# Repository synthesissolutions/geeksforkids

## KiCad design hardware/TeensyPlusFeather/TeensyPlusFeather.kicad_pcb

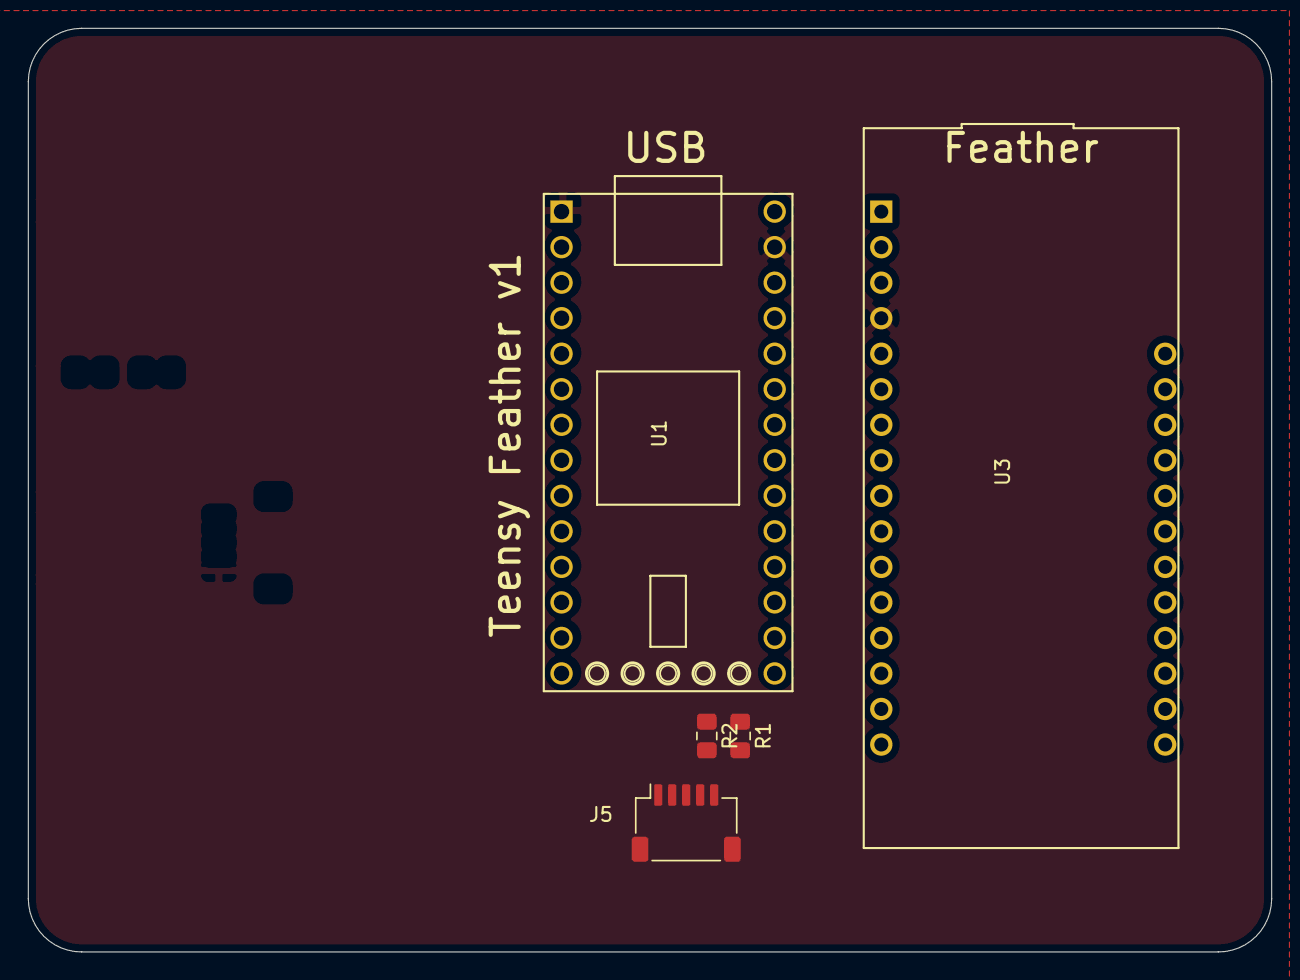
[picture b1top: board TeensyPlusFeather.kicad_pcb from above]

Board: 2 copper layers, 88.9 x 66.0 mm, 5 parts (0 on the bottom side), 21 nets, no tracks yet.

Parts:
J5: I2C; JST_SH_SM05B-SRSS-TB_1x05-1MP_P1.00mm_Horizontal
R1, R2: 10K; R_0805_2012Metric_Pad1.15x1.40mm_HandSolder
U1: Teensy4.0_NoMid; Teensy40_NoMid
U3: OLED Feather; Feather_nRF52840

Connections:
+3V3: J5.2, U1.26, U3.2
+5V: U1.28, U3.26
A0: U1.16, U3.5
A1: U1.17, U3.6
A2: U1.18, U3.7
A3: U1.19, U3.8
D2: U1.4, U3.16
D5: U1.7, U3.19
D6: U1.8, U3.20
D9: U1.11, U3.21
D10: U1.12, U3.22
D11: U1.13, U3.23
GND: J5.1, U1.1, U1.27, U3.4
I2C_SCL: R1.1, U1.21, U3.10, U3.18
I2C_SDA: R2.1, U1.20, U3.9, U3.17
MI: U1.14, U3.13, U3.24
unnamed: J5.3, R2.2
unnamed: J5.4, R1.2
RX: U1.2, U3.14
SCK: U1.15, U3.11, U3.25
TX: U1.3, U3.15

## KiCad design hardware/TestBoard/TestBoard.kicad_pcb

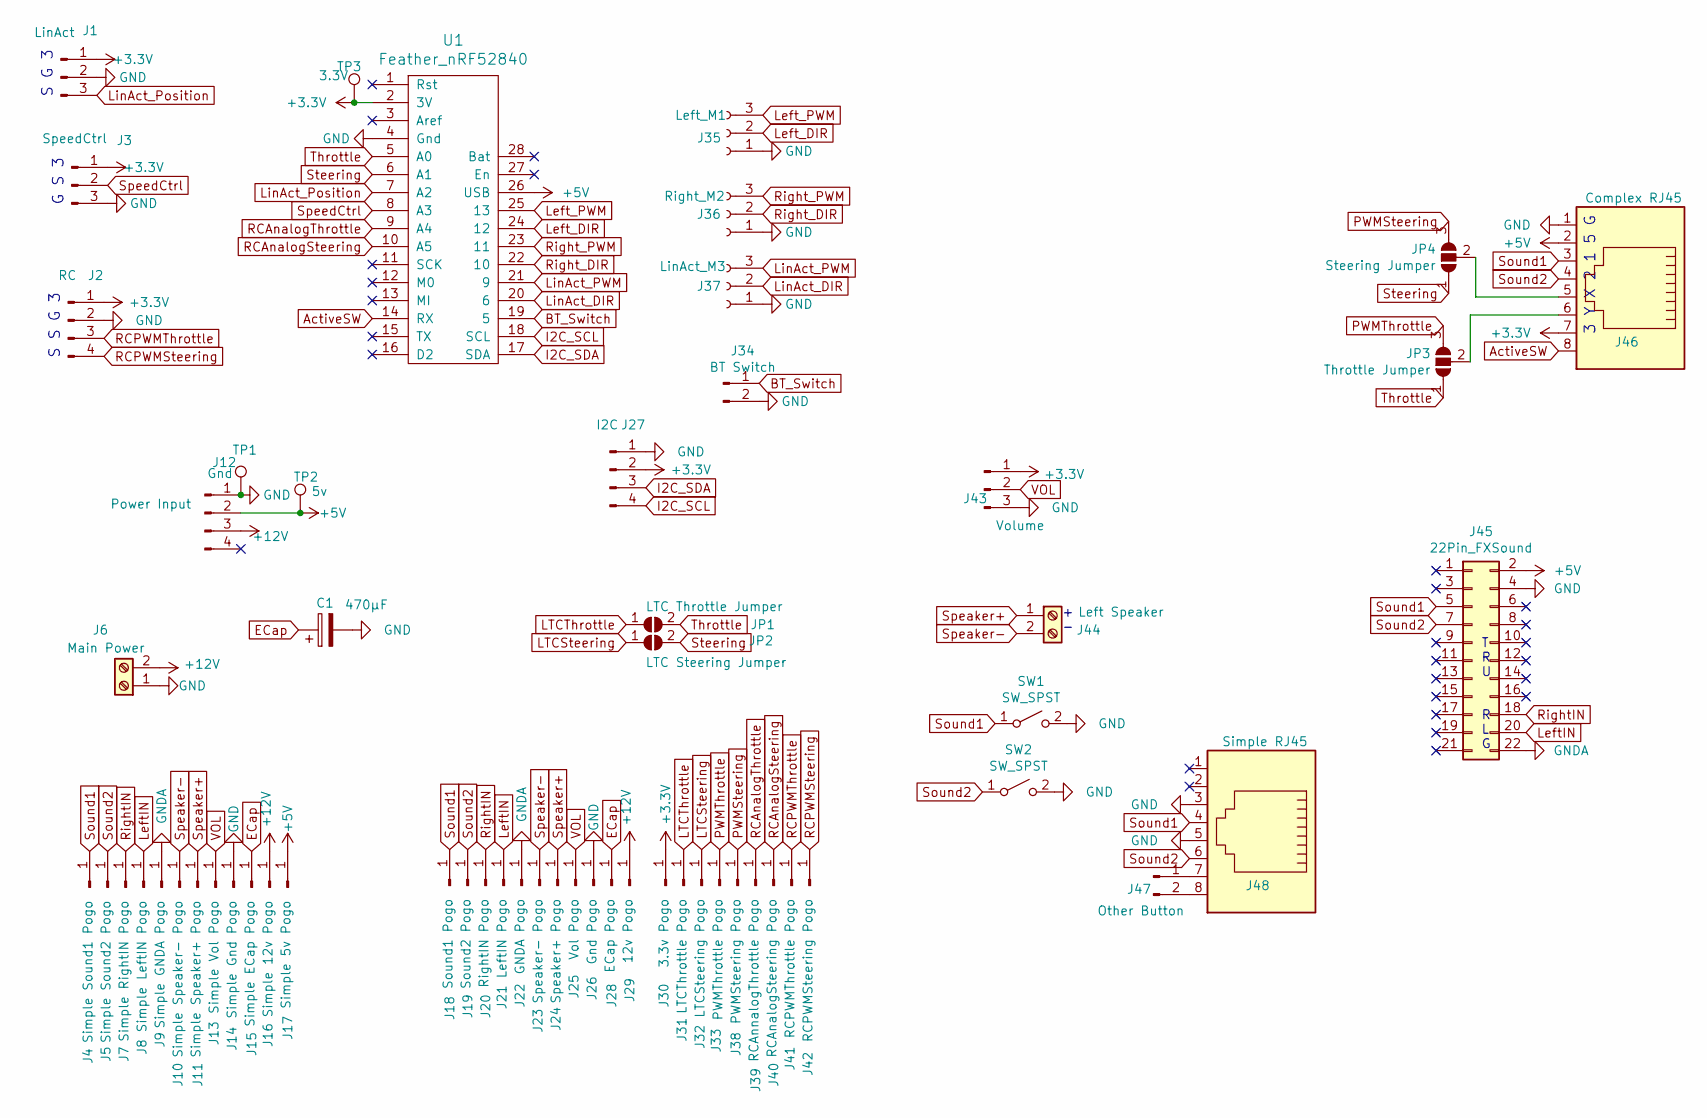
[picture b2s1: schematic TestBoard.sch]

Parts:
C1: 470µF; CP_Radial_D8.0mm_P3.50mm; DigiKey ID 1189-1859-ND
J1: LinAct; PinHeader_1x03_P2.54mm_Vertical
J2: RC; PinHeader_1x04_P2.54mm_Vertical
J3: SpeedCtrl; PinHeader_1x03_P2.54mm_Vertical
J4: Simple Sound1 Pogo; PinHeader_1x01_P2.54mm_Vertical
J5: Simple Sound2 Pogo; PinHeader_1x01_P2.54mm_Vertical
J6: Main Power; TerminalBlock_bornier-2_P5.08mm
J7: Simple RightIN Pogo; PinHeader_1x01_P2.54mm_Vertical
J8: Simple LeftIN Pogo; PinHeader_1x01_P2.54mm_Vertical
J9: Simple GNDA Pogo; PinHeader_1x01_P2.54mm_Vertical
J10: Simple Speaker- Pogo; PinHeader_1x01_P2.54mm_Vertical
J11: Simple Speaker+ Pogo; PinHeader_1x01_P2.54mm_Vertical
J12: Power Input; PinHeader_1x04_P2.54mm_Horizontal
J13: Simple Vol Pogo; PinHeader_1x01_P2.54mm_Vertical
J14: Simple Gnd Pogo; PinHeader_1x01_P2.54mm_Vertical
J15: Simple ECap Pogo; PinHeader_1x01_P2.54mm_Vertical
J16: Simple 12v Pogo; PinHeader_1x01_P2.54mm_Vertical
J17: Simple 5v Pogo; PinHeader_1x01_P2.54mm_Vertical
J18: Sound1 Pogo; PinHeader_1x01_P2.54mm_Vertical
J19: Sound2 Pogo; PinHeader_1x01_P2.54mm_Vertical
J20: RightIN Pogo; PinHeader_1x01_P2.54mm_Vertical
J21: LeftIN Pogo; PinHeader_1x01_P2.54mm_Vertical
J22: GNDA Pogo; PinHeader_1x01_P2.54mm_Vertical
J23: Speaker- Pogo; PinHeader_1x01_P2.54mm_Vertical
J24: Speaker+ Pogo; PinHeader_1x01_P2.54mm_Vertical
J25: Vol Pogo; PinHeader_1x01_P2.54mm_Vertical
J26: Gnd Pogo; PinHeader_1x01_P2.54mm_Vertical
J27: I2C; PinHeader_1x04_P2.54mm_Vertical
J28: ECap Pogo; PinHeader_1x01_P2.54mm_Vertical
J29: 12v Pogo; PinHeader_1x01_P2.54mm_Vertical
J30: 3.3v Pogo; PinHeader_1x01_P2.54mm_Vertical
J31: LTCThrottle Pogo; PinHeader_1x01_P2.54mm_Vertical
J32: LTCSteering Pogo; PinHeader_1x01_P2.54mm_Vertical
J33: PWMThrottle Pogo; PinHeader_1x01_P2.54mm_Vertical
J34: BT Switch; PinHeader_1x02_P2.54mm_Vertical
J35: Left_M1; PinHeader_1x03_P2.54mm_Vertical
J36: Right_M2; PinHeader_1x03_P2.54mm_Vertical
J37: LinAct_M3; PinHeader_1x03_P2.54mm_Vertical
J38: PWMSteering Pogo; PinHeader_1x01_P2.54mm_Vertical
J39: RCAnnalogThrottle Pogo; PinHeader_1x01_P2.54mm_Vertical
J40: RCAnalogSteering Pogo; PinHeader_1x01_P2.54mm_Vertical
J41: RCPWMThrottle Pogo; PinHeader_1x01_P2.54mm_Vertical
J42: RCPWMSteering Pogo; PinHeader_1x01_P2.54mm_Vertical
J43: Volume; PinHeader_1x03_P2.54mm_Vertical
J44: Left Speaker; TerminalBlock_bornier-2_P5.08mm
J45: 22Pin_FXSound; FXSound_2x11_P2.54mm_Short
J46: Complex RJ45; RJ45_x08_Tab_Up
J47: Other Button; PinHeader_1x02_P2.54mm_Vertical
J48: Simple RJ45; RJ45_x08_Tab_Up
JP1: LTC Throttle Jumper; PinHeader_1x02_P2.54mm_Vertical
JP2: LTC Steering Jumper; PinHeader_1x02_P2.54mm_Vertical
JP3: Throttle Jumper; PinHeader_1x03_P2.54mm_Vertical
JP4: Steering Jumper; PinHeader_1x03_P2.54mm_Vertical
SW1, SW2: SW_SPST; SW_PUSH_6mm
TP1: Gnd; TestPoint_Pad_1.5x1.5mm
TP2: 5v; TestPoint_Pad_1.5x1.5mm
TP3: 3.3V; TestPoint_Pad_1.5x1.5mm
U1: Feather_nRF52840

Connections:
+3V3: J1.1, J2.1, J3.1, J27.2, J30.1, J43.1, J46.7, TP3.1, U1.2 (3V)
+5V: J12.2, J17.1, J45.2, J46.2, TP2.1, U1.26 (USB)
+12V: J6.2, J12.3, J16.1, J29.1
ActiveSW: J46.8, U1.14 (RX)
BT_Switch: J34.1, U1.19 (5)
ECap: C1.1, J15.1, J28.1
GND: C1.2, J1.2, J2.2, J3.3, J6.1, J12.1, J14.1, J26.1, J27.1, J34.2, J35.1, J36.1, J37.1, J43.3, J45.4, J46.1, J48.3, J48.5, SW1.2 (B), SW2.2 (B), TP1.1, U1.4 (Gnd)
GNDA: J9.1, J22.1, J45.22
I2C_SCL: J27.4, U1.18 (SCL)
I2C_SDA: J27.3, U1.17 (SDA)
LTCSteering: J32.1, JP2.1 (A)
LTCThrottle: J31.1, JP1.1 (A)
LeftIN: J8.1, J21.1, J45.20
Left_DIR: J35.2, U1.24 (12)
Left_PWM: J35.3, U1.25 (13)
LinAct_DIR: J37.2, U1.20 (6)
LinAct_PWM: J37.3, U1.21 (9)
LinAct_Position: J1.3, U1.7 (A2)
unnamed: J46.5, JP4.2 (C)
unnamed: J46.6, JP3.2 (C)
unnamed: J47.1, J48.7
unnamed: J47.2, J48.8
PWMSteering: J38.1, JP4.3 (B)
PWMThrottle: J33.1, JP3.3 (B)
RCAnalogSteering: J40.1, U1.10 (A5)
RCAnalogThrottle: J39.1, U1.9 (A4)
RCPWMSteering: J2.4, J42.1
RCPWMThrottle: J2.3, J41.1
RightIN: J7.1, J20.1, J45.18
Right_DIR: J36.2, U1.22 (10)
Right_PWM: J36.3, U1.23 (11)
Sound1: J4.1, J18.1, J45.5, J46.3, J48.4, SW1.1 (A)
Sound2: J5.1, J19.1, J45.7, J46.4, J48.6, SW2.1 (A)
Speaker+: J11.1, J24.1, J44.1
Speaker-: J10.1, J23.1, J44.2
SpeedCtrl: J3.2, U1.8 (A3)
Steering: JP2.2 (B), JP4.1 (A), U1.6 (A1)
Throttle: JP1.2 (B), JP3.1 (A), U1.5 (A0)
VOL: J13.1, J25.1, J43.2

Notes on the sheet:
3 Y X 2 1 5 G
S S G 3
G S 3
S G 3
R L G
T R U
+ -

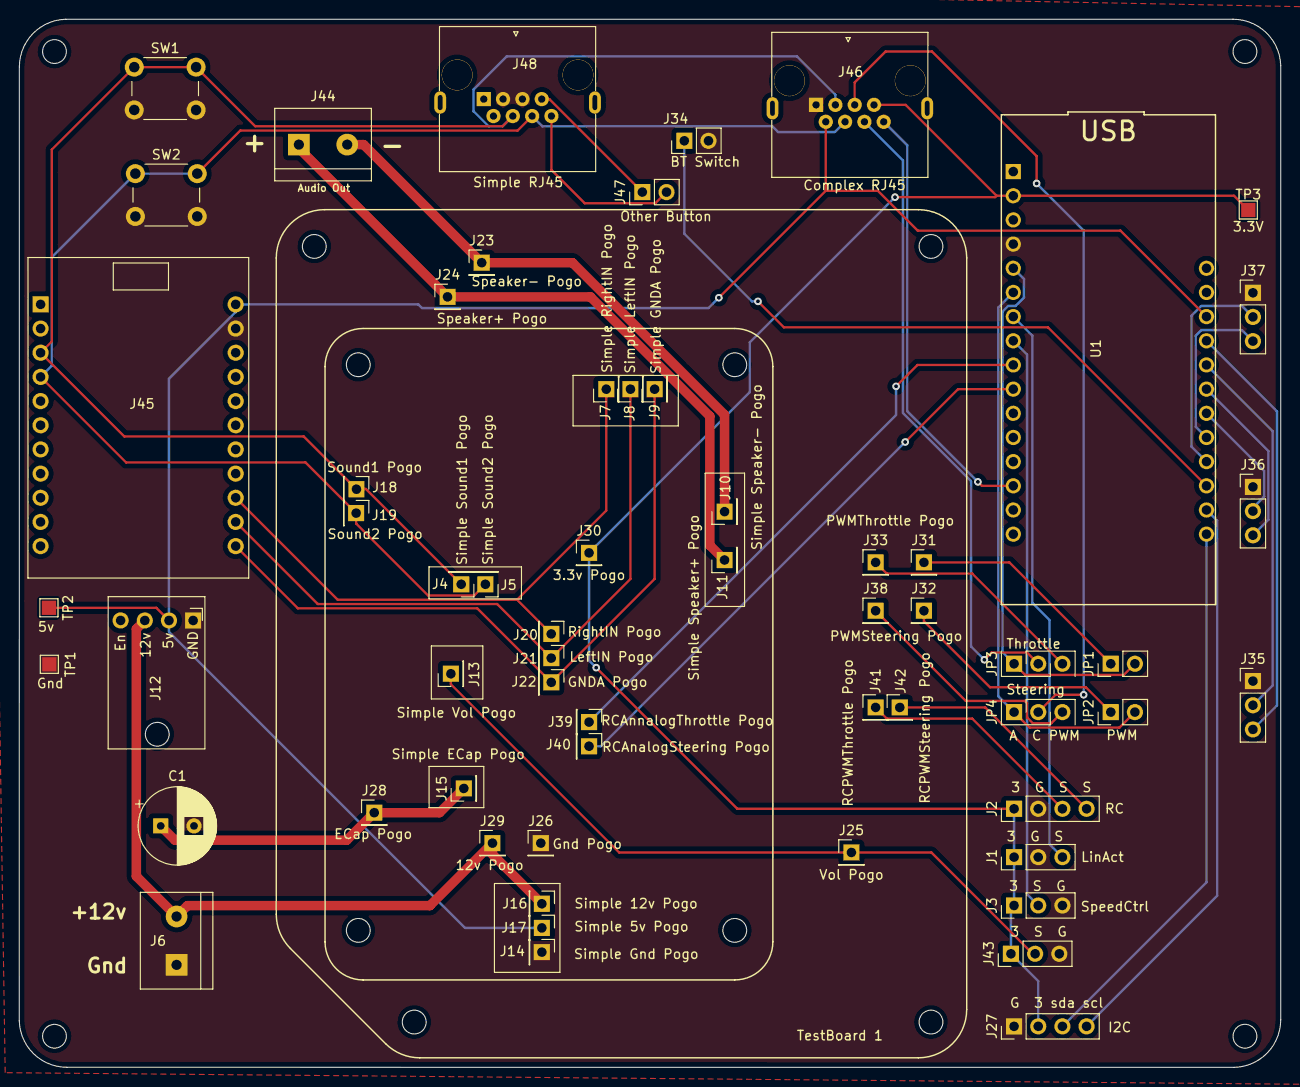
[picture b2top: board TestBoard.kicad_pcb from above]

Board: 2 copper layers, 132.6 x 110.1 mm, 63 parts (0 on the bottom side), 39 nets.

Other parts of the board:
REF: MountingHole_2.5mm
REF#2, REF#3, REF#4: MountingHole_2.5mm

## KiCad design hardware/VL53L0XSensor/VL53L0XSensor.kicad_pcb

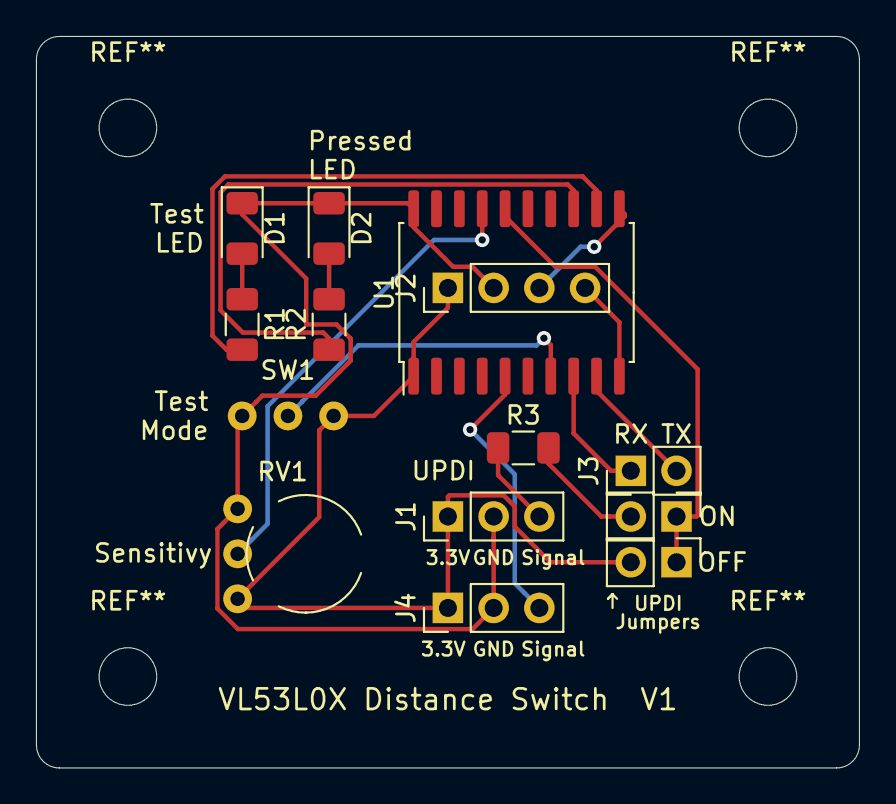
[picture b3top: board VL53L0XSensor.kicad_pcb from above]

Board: 2 copper layers, 45.7 x 40.6 mm, 14 parts (0 on the bottom side), 16 nets.

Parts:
D1: Mode LED; LED_1206_3216Metric
D2: Button LED; LED_1206_3216Metric
J1, J4: Conn_01x03_Male; PinHeader_1x03_P2.54mm_Vertical
J2: Conn_01x04_Female; PinHeader_1x04_P2.54mm_Vertical
J3: Conn_01x02_Male; PinHeader_1x02_P2.54mm_Vertical
OFF: Jumper_NO_Small; PinHeader_1x02_P2.54mm_Vertical
ON: Jumper_NO_Small; PinHeader_1x02_P2.54mm_Vertical
R1, R2: 220; R_1206_3216Metric
R3: 4.7k; R_1206_3216Metric
RV1: R_POT; Potentiometer_Small_Blue
SW1: SW_SPDT; Switch_THT_SPDT
U1: ATtiny3216-S; SOIC-20W_7.5x12.8mm_P1.27mm

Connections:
+3V3: J1.1, J2.1, J4.1, OFF.2, RV1.1, SW1.3, U1.1
GND: D1.1, D2.1, J1.2, J2.2, J4.2, RV1.3, SW1.1, U1.20
unnamed: D1.2, R1.1
unnamed: D2.2, R2.2
unnamed: J1.3, R3.1
unnamed: J2.3, U1.11
unnamed: J2.4, U1.10
unnamed: J3.1, U1.8
unnamed: J3.2, U1.9
unnamed: J4.3, U1.5
unnamed: OFF.1, ON.1, U1.16
unnamed: ON.2, R3.2
unnamed: R1.2, U1.12
unnamed: R2.1, U1.13
unnamed: RV1.2, U1.17
unnamed: SW1.2, U1.7

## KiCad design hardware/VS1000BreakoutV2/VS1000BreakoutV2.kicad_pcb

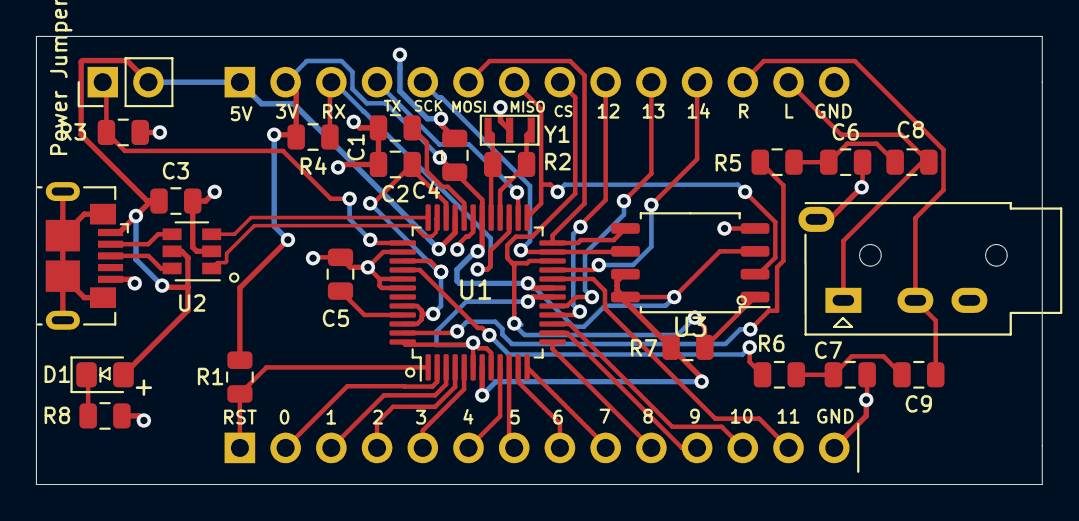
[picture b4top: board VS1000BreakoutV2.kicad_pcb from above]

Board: 2 copper layers, 55.9 x 24.9 mm, 27 parts (0 on the bottom side), 42 nets.

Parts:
C1, C2, C3, C4, C8, C9: 10uF; C_0805_2012Metric
C5: 1uF; C_0805_2012Metric
C6, C7: 4.7nF; C_0805_2012Metric
D1: Power; LED_0805_2012Metric_Pad1.15x1.40mm_HandSolder
J1: Power Jumper; PinHeader_1x02_P2.54mm_Vertical
J2, J4: Conn_01x14_Male; PinHeader_1x14_P2.54mm_Vertical
J3: USB_B_Micro; USB_Micro-B_GCT_USB3076-30-A
J5: AudioJack4; Jack_3.5mm_PJ320A_Horizontal
R1, R4, R7: 100K; R_0805_2012Metric
R2, R3: 1M; R_0805_2012Metric
R5, R6, R8: 470; R_0805_2012Metric
U1: VS1000; LQFP-48_7x7mm_P0.5mm
U2: USBLC6-2SC6; SOT-23-6
U3: MX25L6473FM2I-08G; SOIC-8_5.275x5.275mm_P1.27mm
Y1: 12MHz; Resonator

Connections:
+5V: C3.1, D1.2, J1.2, J3.1, J4.1, U1.33, U2.5
CS: J4.8, R7.2, U1.22, U3.1
GND: C1.2, C2.2, C3.2, C4.1, C5.1, C6.2, C7.2, J2.14, J3.5, J4.14, J5.S, R3.2, R8.2, U1.6, U1.8, U1.18, U1.31, U1.38, U1.41, U1.42, U1.48, U2.2, U3.4, Y1.2
GPIO_0: J2.2, U1.2
GPIO_1: J2.3, U1.3
GPIO_2: J2.4, U1.4
GPIO_3: J2.5, U1.5
GPIO_4: J2.6, U1.9
GPIO_5: J2.7, U1.10
GPIO_6: J2.8, U1.11
GPIO_7: J2.9, U1.12
GPIO_8: J2.10, U1.13
GPIO_9: J2.11, U1.14
GPIO_10: J2.12, U1.15
GPIO_11: J2.13, U1.20
GPIO_12: J4.9, U1.16
GPIO_13: J4.10, U1.17
GPIO_14: J4.11, U1.21
LEFT: R5.2, U1.47
L_AC: C8.1, J4.13, J5.T
MISO: J4.7, U1.25, U3.2
MOSI: J4.6, U1.24, U3.5
unnamed: C4.2, U1.32
unnamed: C5.2, U1.45
unnamed: C6.1, C8.2, R5.1
unnamed: C7.1, C9.2, R6.1
unnamed: D1.1, R8.1
unnamed: J1.1, R3.1, U1.37
unnamed: R2.1, U1.29, Y1.3
unnamed: R2.2, U1.28, Y1.1
RESET: J2.1, R1.1, U1.1
RIGHT: R6.2, U1.40
RX: J4.3, R4.1, U1.27
R_AC: C9.1, J4.12, J5.R1
SCK: J4.5, U1.23, U3.6
TX: J4.4, U1.26
USB_CONN_D+: J3.3, U2.6
USB_CONN_D-: J3.2, U2.4
USB_D+: U1.35, U2.1
USB_D-: U1.36, U2.3
VDD: C1.1, J4.2, R1.2, R4.2, R7.1, U1.7, U1.19, U1.30, U3.3, U3.7, U3.8
VDDA: C2.1, U1.34, U1.39, U1.44, U1.46

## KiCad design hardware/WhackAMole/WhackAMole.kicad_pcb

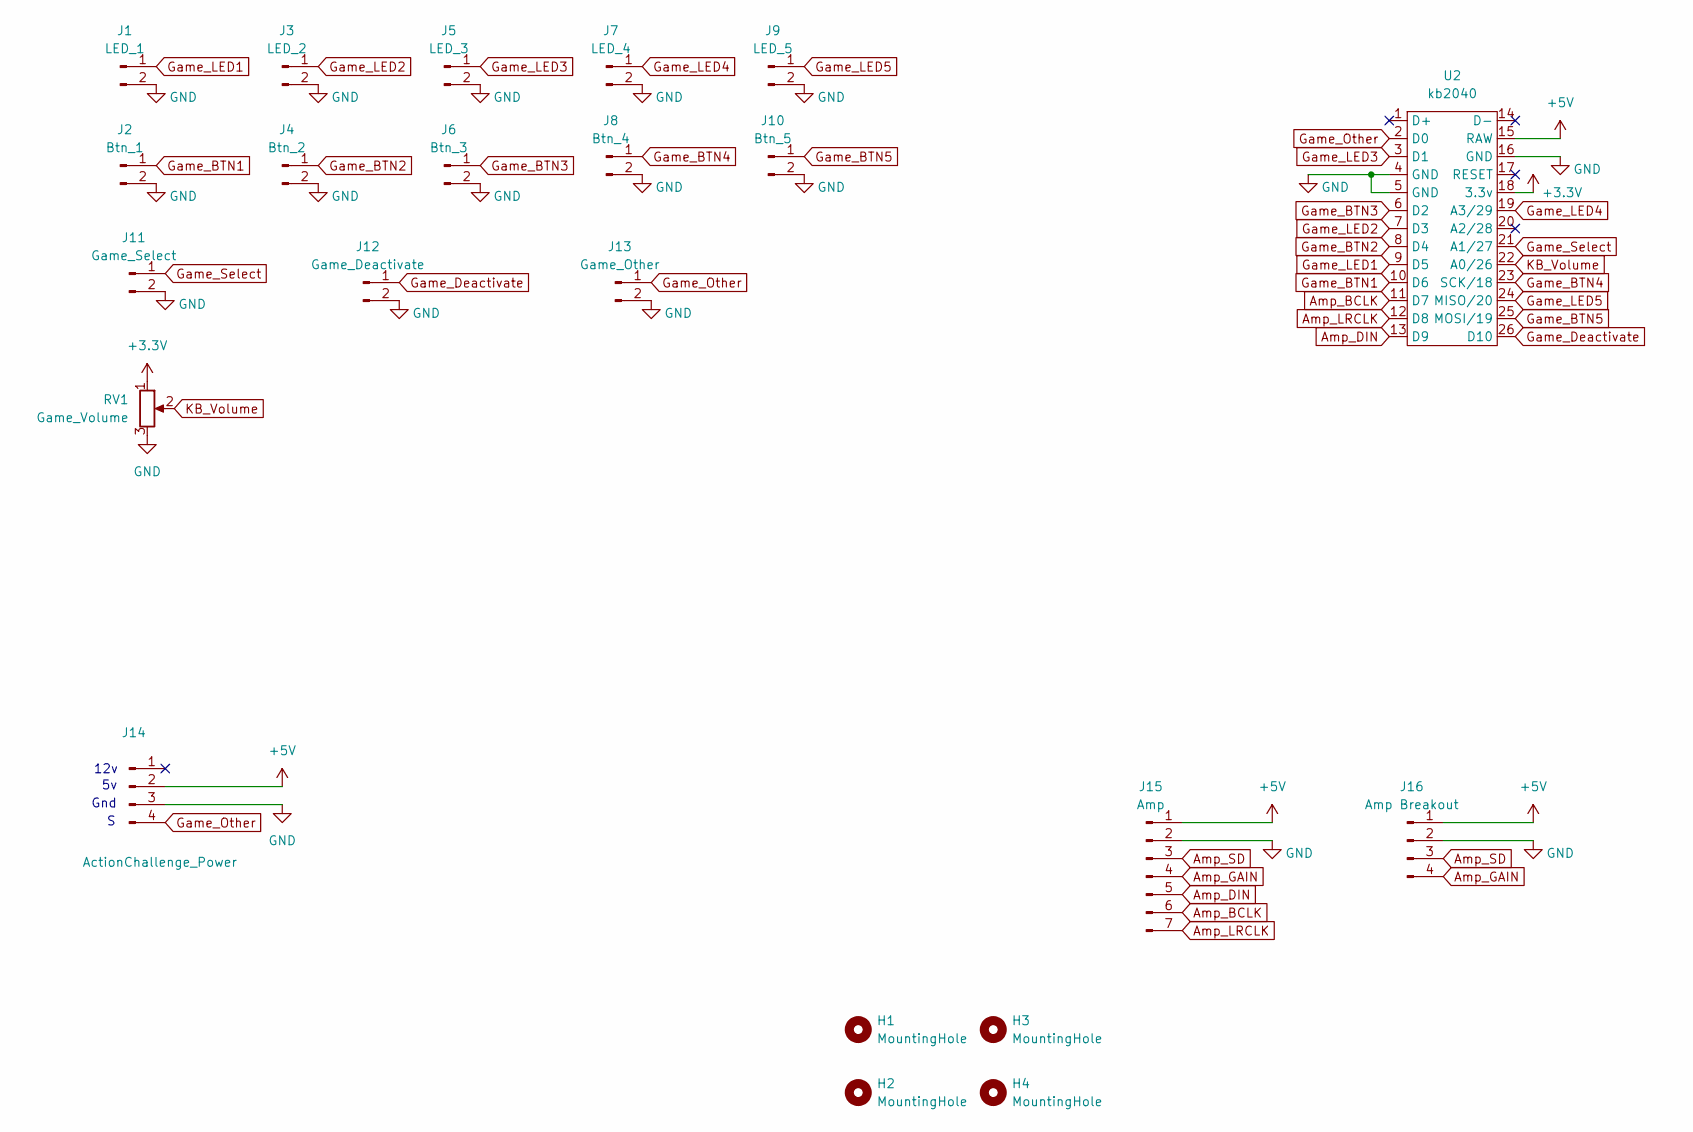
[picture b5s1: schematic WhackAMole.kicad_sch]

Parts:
H1, H2, H3, H4: MountingHole; MountingHole_2.7mm_M2.5
J1: LED_1; JST_XH_B2B-XH-A_1x02_P2.50mm_Vertical
J2: Btn_1; JST_XH_B2B-XH-A_1x02_P2.50mm_Vertical
J3: LED_2; JST_XH_B2B-XH-A_1x02_P2.50mm_Vertical
J4: Btn_2; JST_XH_B2B-XH-A_1x02_P2.50mm_Vertical
J5: LED_3; JST_XH_B2B-XH-A_1x02_P2.50mm_Vertical
J6: Btn_3; JST_XH_B2B-XH-A_1x02_P2.50mm_Vertical
J7: LED_4; JST_XH_B2B-XH-A_1x02_P2.50mm_Vertical
J8: Btn_4; JST_XH_B2B-XH-A_1x02_P2.50mm_Vertical
J9: LED_5; JST_XH_B2B-XH-A_1x02_P2.50mm_Vertical
J10: Btn_5; JST_XH_B2B-XH-A_1x02_P2.50mm_Vertical
J11: Game_Select; JST_XH_B2B-XH-A_1x02_P2.50mm_Vertical
J12: Game_Deactivate; JST_XH_B2B-XH-A_1x02_P2.50mm_Vertical
J13: Game_Other; PinSocket_1x02_P2.54mm_Vertical
J14: ActionChallenge_Power; JST_XH_B4B-XH-A_1x04_P2.50mm_Vertical
J15: Amp; Adafruit_Max98357A_Breakout
J16: Amp Breakout; PinHeader_1x04_P2.54mm_Vertical
RV1: Game_Volume; JST_XH_B3B-XH-A_1x03_P2.50mm_Vertical
U2: kb2040

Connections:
+3.3V: RV1.1, U2.18 (3.3v)
+5V: J14.2, J15.1, J16.1, U2.15 (RAW)
Amp_BCLK: J15.6, U2.11 (D7)
Amp_DIN: J15.5, U2.13 (D9)
Amp_GAIN: J15.4, J16.4
Amp_LRCLK: J15.7, U2.12 (D8)
Amp_SD: J15.3, J16.3
GND: J1.2, J2.2, J3.2, J4.2, J5.2, J6.2, J7.2, J8.2, J9.2, J10.2, J11.2, J12.2, J13.2, J14.3, J15.2, J16.2, RV1.3, U2.4 (GND), U2.5 (GND), U2.16 (GND)
Game_BTN1: J2.1, U2.10 (D6)
Game_BTN2: J4.1, U2.8 (D4)
Game_BTN3: J6.1, U2.6 (D2)
Game_BTN4: J8.1, U2.23 (SCK/18)
Game_BTN5: J10.1, U2.25 (MOSI/19)
Game_Deactivate: J12.1, U2.26 (D10)
Game_LED1: J1.1, U2.9 (D5)
Game_LED2: J3.1, U2.7 (D3)
Game_LED3: J5.1, U2.3 (D1)
Game_LED4: J7.1, U2.19 (A3/29)
Game_LED5: J9.1, U2.24 (MISO/20)
Game_Other: J13.1, J14.4, U2.2 (D0)
Game_Select: J11.1, U2.21 (A1/27)
KB_Volume: RV1.2, U2.22 (A0/26)

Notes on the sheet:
Gnd
12v

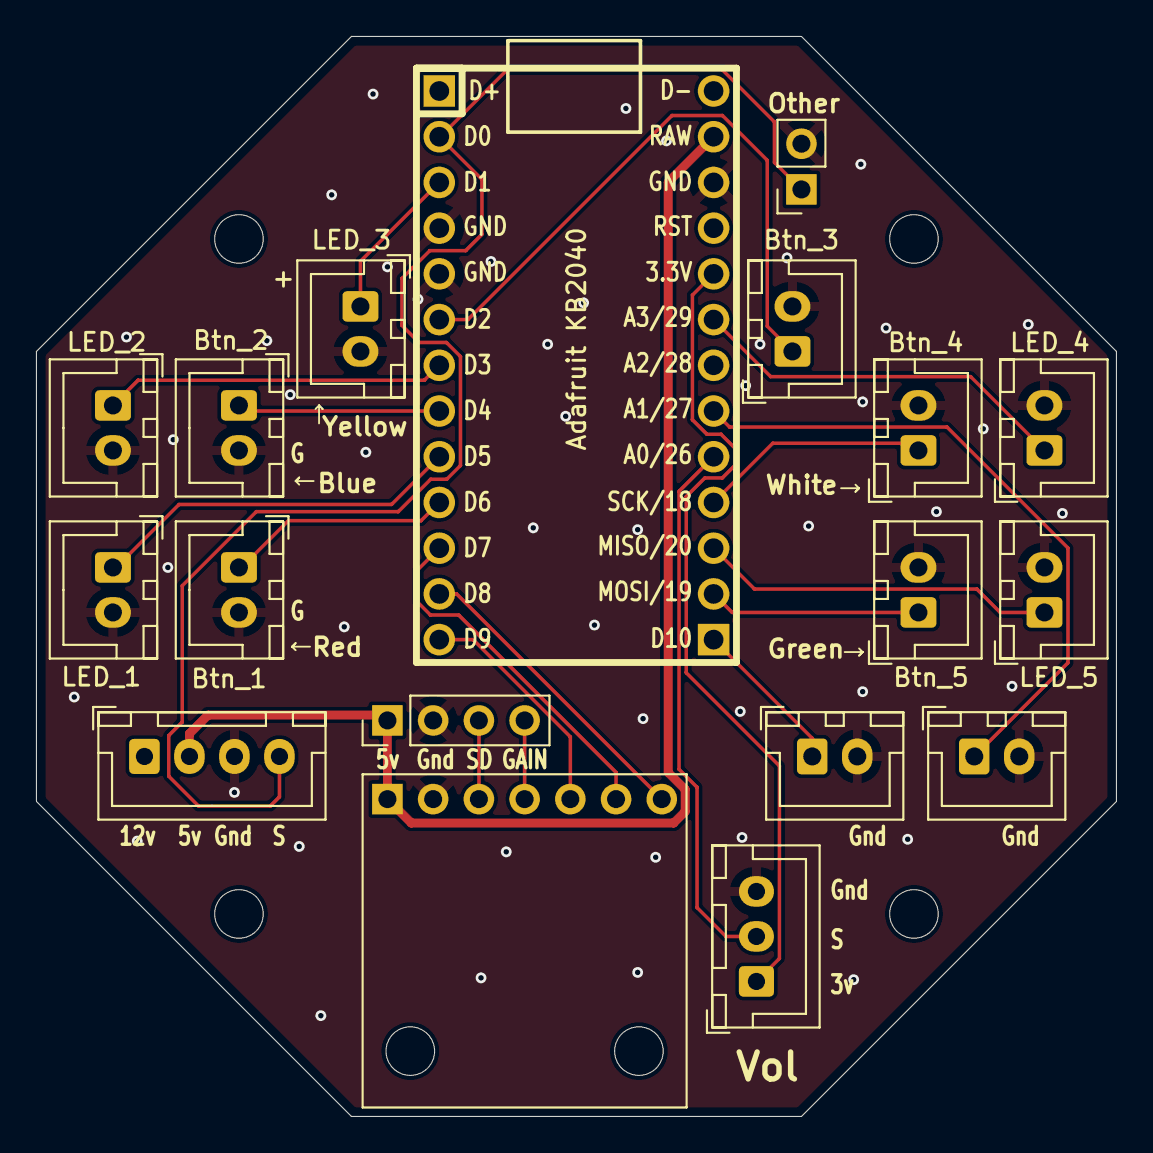
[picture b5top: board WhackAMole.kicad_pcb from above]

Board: 2 copper layers, 60.0 x 60.0 mm, 22 parts (0 on the bottom side), 22 nets.

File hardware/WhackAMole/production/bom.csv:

Designator,Footprint,Quantity,Value,LCSC Part #
J1,JST_XH_B2B-XH-A_1x02_P2.50mm_Vertical,1,LED_1,
J10,JST_XH_B2B-XH-A_1x02_P2.50mm_Vertical,1,Btn_5,
J11,JST_XH_B2B-XH-A_1x02_P2.50mm_Vertical,1,Game_Select,
J12,JST_XH_B2B-XH-A_1x02_P2.50mm_Vertical,1,Game_Deactivate,
J13,PinSocket_1x02_P2.54mm_Vertical,1,Game_Other,
J14,JST_XH_B4B-XH-A_1x04_P2.50mm_Vertical,1,ActionChallenge_Power,
J15,Adafruit_Max98357A_Breakout,1,Amp,
J16,PinHeader_1x04_P2.54mm_Vertical,1,Amp Breakout,
J2,JST_XH_B2B-XH-A_1x02_P2.50mm_Vertical,1,Btn_1,
J3,JST_XH_B2B-XH-A_1x02_P2.50mm_Vertical,1,LED_2,
J4,JST_XH_B2B-XH-A_1x02_P2.50mm_Vertical,1,Btn_2,
J5,JST_XH_B2B-XH-A_1x02_P2.50mm_Vertical,1,LED_3,
J6,JST_XH_B2B-XH-A_1x02_P2.50mm_Vertical,1,Btn_3,
J7,JST_XH_B2B-XH-A_1x02_P2.50mm_Vertical,1,LED_4,
J8,JST_XH_B2B-XH-A_1x02_P2.50mm_Vertical,1,Btn_4,
J9,JST_XH_B2B-XH-A_1x02_P2.50mm_Vertical,1,LED_5,
RV1,JST_XH_B3B-XH-A_1x03_P2.50mm_Vertical,1,Game_Volume,
U2,kb2040,1,kb2040,

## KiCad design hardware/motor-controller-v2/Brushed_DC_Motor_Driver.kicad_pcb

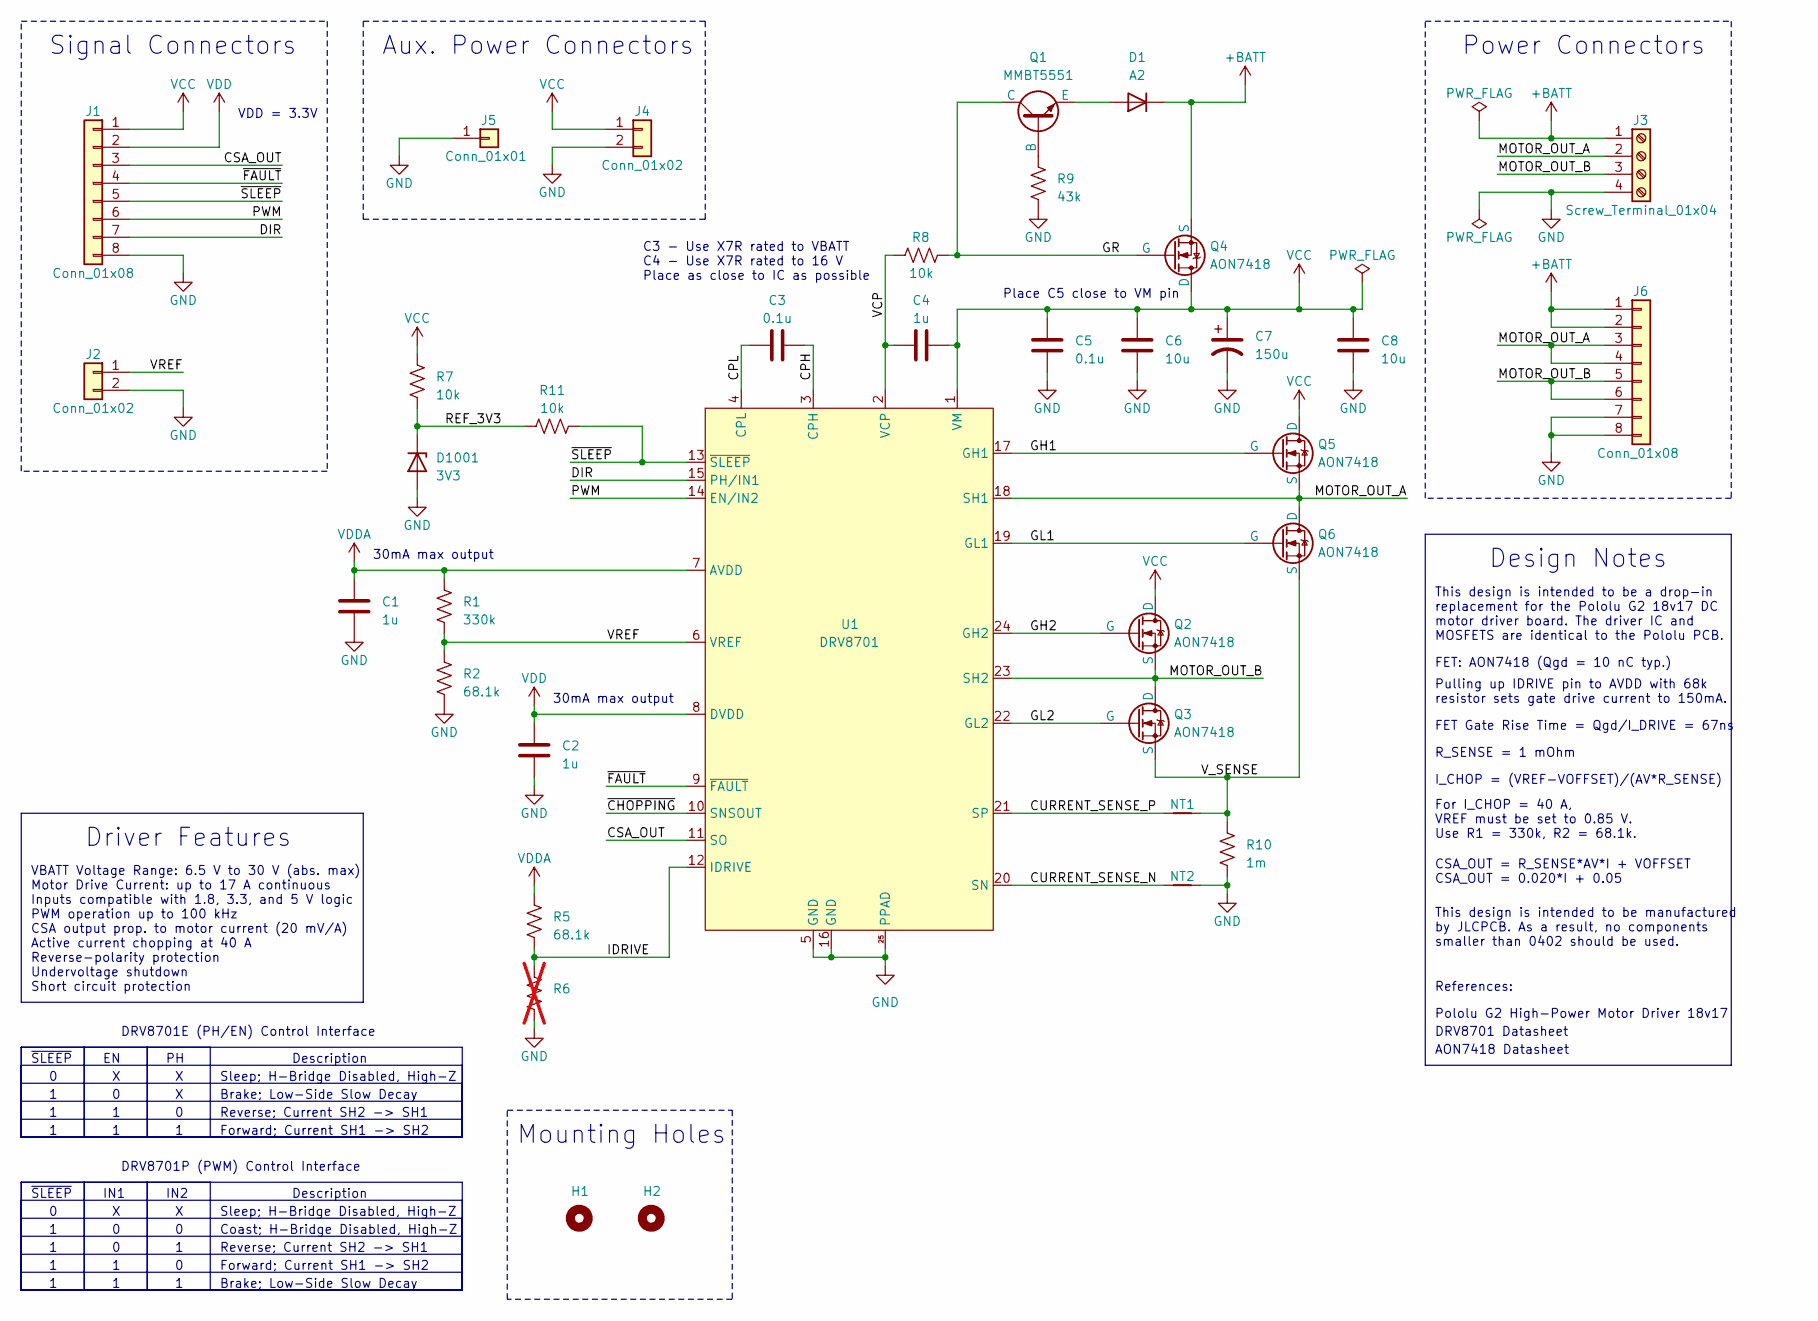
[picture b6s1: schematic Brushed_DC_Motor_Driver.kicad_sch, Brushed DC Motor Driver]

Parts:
C1, C2, C4: 1u; C_0402_1005Metric; MPN C29266
C3, C5: 0.1u; C_0402_1005Metric; MPN C343047
C6, C8: 10u; C_0805_2012Metric; MPN C162422
C7: 150u; CP_Elec_6.3x7.7; MPN C249984
D1: A2; D_SOD-123F; MPN C169542
D1001: 3V3; D_SOD-523
H1, H2: MountingHole_Pad; MountingHole_2.2mm_M2
J1, J6: Conn_01x08; PinHeader_1x08_P2.54mm_Vertical
J2: Conn_01x02; PinHeader_1x02_P2.54mm_Vertical
J3: Screw_Terminal_01x04; CUI_TB004-508-04BE
J4: Conn_01x02; PinHeader_1x02_P5.00mm_Vertical
J5: Conn_01x01; PinHeader_1x01_P2.54mm_Vertical
NT1, NT2: NetTie_2; NetTie-2_SMD_Pad0.2mm
Q1: MMBT5551; SOT-23; MPN C2926169
Q2, Q3, Q4, Q5, Q6: AON7418; MPN C74384
R1: 330k; R_0402_1005Metric; MPN C138006
R2, R5: 68.1k; R_0402_1005Metric; MPN C276276
R6: R_0402_1005Metric; not fitted
R7, R8, R11: 10k; R_0402_1005Metric; MPN C60490
R9: 43k; R_0402_1005Metric; MPN C8329
R10: 1m; R_1206_3216Metric; MPN C393098
U1: DRV8701; RGE0024F; MPN C90964

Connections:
+BATT: D1.1 (K), J3.1, J6.1, J6.2, Q4.1 (S), Q4.2 (S), Q4.3 (S)
/CPH: C3.2, U1.3 (CPH)
/CPL: C3.1, U1.4 (CPL)
/CSA_OUT: J1.3, U1.11 (SO)
/CURRENT_SENSE_N: NT2.1, U1.20 (SN)
/CURRENT_SENSE_P: NT1.2, U1.21 (SP)
/DIR: J1.7, U1.15 (PH/IN1)
/GH1: Q5.4 (G), U1.17 (GH1)
/GH2: Q2.4 (G), U1.24 (GH2)
/GL1: Q6.4 (G), U1.19 (GL1)
/GL2: Q3.4 (G), U1.22 (GL2)
/GR: Q1.1 (C), Q4.4 (G), R8.2
/IDRIVE: R5.2, R6.1, U1.12 (IDRIVE)
/MOTOR_OUT_A: J3.2, J6.3, J6.4, Q5.1 (S), Q5.2 (S), Q5.3 (S), Q6.5 (D), Q6.6 (D), Q6.7 (D), Q6.8 (D), Q6.9 (D), U1.18 (SH1)
/MOTOR_OUT_B: J3.3, J6.5, J6.6, Q2.1 (S), Q2.2 (S), Q2.3 (S), Q3.5 (D), Q3.6 (D), Q3.7 (D), Q3.8 (D), Q3.9 (D), U1.23 (SH2)
/PWM: J1.6, U1.14 (EN/IN2)
/REF_3V3: D1001.1 (K), R7.2, R11.1
/VCP: C4.1, R8.1, U1.2 (VCP)
/VREF: J2.1, R1.2, R2.1, U1.6 (VREF)
/V_SENSE: NT1.1, Q3.1 (S), Q3.2 (S), Q3.3 (S), Q6.1 (S), Q6.2 (S), Q6.3 (S), R10.1
/~CHOPPING: U1.10 (SNSOUT)
/~FAULT: J1.4, U1.9 (~FAULT)
/~SLEEP: J1.5, R11.2, U1.13 (~SLEEP)
GND: C1.1, C2.1, C5.1, C6.1, C7.2, C8.1, D1001.2 (A), J1.8, J2.2, J3.4, J4.2, J5.1, J6.7, J6.8, NT2.2, R2.2, R6.2, R9.2, R10.2, U1.5 (GND), U1.16 (GND), U1.25 (PPAD)
unnamed: D1.2 (A), Q1.3 (E)
unnamed: Q1.2 (B), R9.1
VCC: C4.2, C5.2, C6.2, C7.1, C8.2, J1.1, J4.1, Q2.5 (D), Q2.6 (D), Q2.7 (D), Q2.8 (D), Q2.9 (D), Q4.5 (D), Q4.6 (D), Q4.7 (D), Q4.8 (D), Q4.9 (D), Q5.5 (D), Q5.6 (D), Q5.7 (D), Q5.8 (D), Q5.9 (D), R7.1, U1.1 (VM)
VDD: C2.2, J1.2, U1.8 (DVDD)
VDDA: C1.2, R1.1, R5.1, U1.7 (AVDD)

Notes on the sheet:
Aux. Power Connectors
Reverse; Current SH2 -> SH1
Design Notes
This design is intended to be a drop-in replacement for the Pololu G2 18v17 DC motor driver board. The driver IC and MOSFETS are identical to the Pololu PCB.
Brake; Low-Side Slow Decay
CSA_OUT = R_SENSE*AV*I + VOFFSET CSA_OUT = 0.020*I + 0.05
~{SLEEP}
Sleep; H-Bridge Disabled, High-Z
Description
This design is intended to be manufactured by JLCPCB. As a result, no components smaller than 0402 should be used.
IN2
Power Connectors
IN1
FET: AON7418 (Qgd = 10 nC typ.)
AON7418 Datasheet
Forward; Current SH1 -> SH2
Driver Features
DRV8701P (PWM) Control Interface
30mA max output
DRV8701E (PH/EN) Control Interface
R_SENSE = 1 mOhm
Mounting Holes
C3 - Use X7R rated to VBATT C4 - Use X7R rated to 16 V Place as close to IC as possible
VDD = 3.3V
DRV8701 Datasheet
Pulling up IDRIVE pin to AVDD with 68k resistor sets gate drive current to 150mA.
References:
Coast; H-Bridge Disabled, High-Z
Signal Connectors
For I_CHOP = 40 A, VREF must be set to 0.85 V. Use R1 = 330k, R2 = 68.1k.
Place C5 close to VM pin
VBATT Voltage Range: 6.5 V to 30 V (abs. max) Motor Drive Current: up to 17 A continuous Inputs compatible with 1.8, 3.3, and 5 V logic PWM operation up to 100 kHz CSA output prop. to motor current (20 mV/A) Active current chopping at 40 A Reverse-polarity protection Undervoltage shutdown Short cir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
Pololu G2 High-Power Motor Driver 18v17
I_CHOP = (VREF-VOFFSET)/(AV*R_SENSE)
FET Gate Rise Time = Qgd/I_DRIVE = 67ns

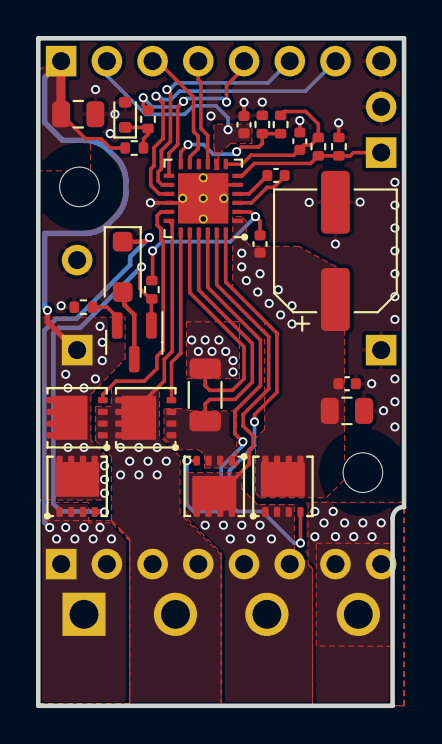
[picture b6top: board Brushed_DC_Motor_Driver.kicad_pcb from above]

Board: 2 copper layers, 20.3 x 37.1 mm, 36 parts (0 on the bottom side), 28 nets.

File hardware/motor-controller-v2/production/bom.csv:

Designator,Footprint,Quantity,Value,LCSC Part #
"C1, C2, C4",0402,3,1u,C29266
"C3, C5",0402,2,0.1u,C343047
"C6, C8",0805,2,10u,C162422
C7,CP_Elec_6.3x7.7,1,150u,C249984
D1,D_SOD-123F,1,A2,C169542
Q1,SOT-23,1,MMBT5551,C2926169
"Q2, Q3, Q4, Q5, Q6",AON7418,5,AON7418,C74384
R1,0402,1,330k,C138006
R10,1206,1,1m,C393098
"R2, R5",0402,2,68.1k,C276276
"R3, R4, R7, R8",0402,4,10k,C60490
R9,0402,1,43k,C8329
U1,RGE0024F,1,DRV8701,C90964
